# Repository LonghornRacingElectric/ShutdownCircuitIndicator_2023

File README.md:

# ShutdownCircuitIndicator_2023

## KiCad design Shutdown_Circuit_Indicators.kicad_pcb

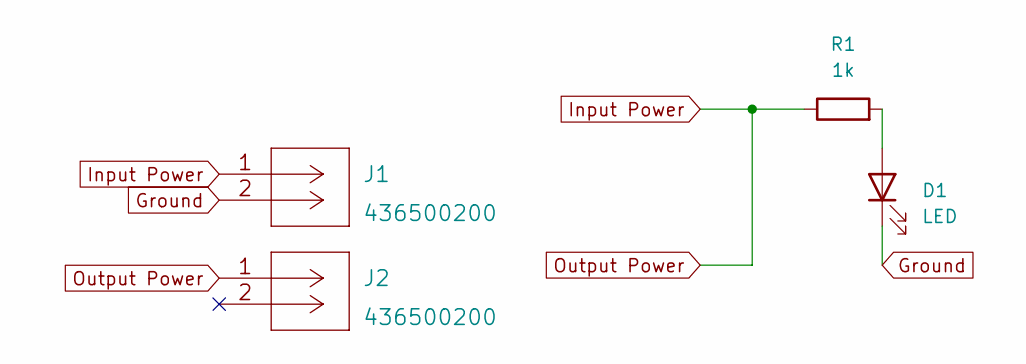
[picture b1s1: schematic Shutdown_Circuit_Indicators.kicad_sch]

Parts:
D1: LED; D_T-1_P5.08mm_Horizontal
J1, J2: 436500200
R1: 1k; R_0603_1608Metric_Pad0.98x0.95mm_HandSolder

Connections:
Ground: D1.1 (K), J1.2
Input Power: J1.1, J2.1, R1.1
unnamed: D1.2 (A), R1.2

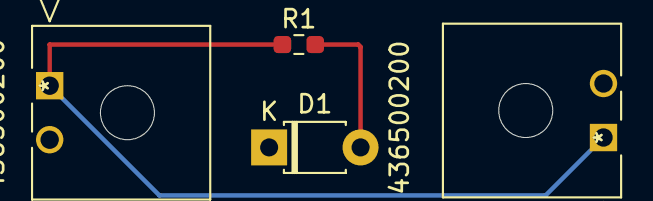
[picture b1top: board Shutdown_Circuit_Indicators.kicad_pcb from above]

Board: 2 copper layers, 4 parts (0 on the bottom side), 3 nets.

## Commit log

2022-09-26 Added 2023KicadLibrary
2022-11-06 Add files via upload
    Updated Shutdown Circuit Indicators
2022-11-07 Add files via upload
    added datasheet
2022-11-13 Add files via upload
    Updated Datasheet

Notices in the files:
parts and their libraries:
Copyright 2021 Accelerated Designs. All rights reserved.
